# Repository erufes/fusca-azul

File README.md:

# Fusca Azul

Nova versão do robô Fusca Azul, da ERUS/UFES. O software e o hardware estão
em atualização. O reconhecimento de gestos agora usa um aplicativo desktop
em Qt, com servidor local de comandos e configuração do Wi-Fi do robô pelo navegador.

## Executar

Requer Python 3.14 ou superior, [uv](https://docs.astral.sh/uv/) e uma webcam.
Na raiz do projeto:

```bash
uv run gestos
```

No Ubuntu, Debian ou Linux Mint, instale também a biblioteca de cursor usada
pelo Qt no X11:

```bash
sudo apt-get install libxcb-cursor0
```

O uv instala as dependências e abre a janela. Na primeira execução, o aplicativo
baixa o modelo do MediaPipe, caso ele ainda não esteja disponível. As próximas
execuções podem funcionar sem internet, com as dependências e o modelo instalados.
Permita o acesso à câmera nas configurações de privacidade do sistema, se necessário.

A interface mostra a câmera espelhada, os pontos da mão, o gesto reconhecido e o
modo selecionado. Para usar outra webcam, abra a engrenagem no canto superior direito,
selecione a câmera pelo nome e clique em **Aplicar**. Se a captura estiver ativa,
o aplicativo troca a câmera automaticamente. Use **Atualizar lista** depois
de conectar ou desconectar uma webcam.

Python, Qt e MediaPipe têm versões para Linux, Windows e macOS, mas a combinação
de versões e arquitetura precisa ser compatível. No Linux, o Qt pode exigir
bibliotecas gráficas do sistema. Não há empacotamento nem Docker.

**Os gestos controlam o robô por Wi-Fi.** O aplicativo anuncia o servidor por
mDNS, e o robô o encontra automaticamente. A troca de modo pelo gesto de rock
está desabilitada, e o aplicativo permanece no modo Gestos. A navegação autônoma
ainda não foi implementada.

Veja [configuração de Wi-Fi e protocolo](docs/comunicacao.md) para conectar o robô.

## Firmware do robô

O NodeMCU/ESP8266 controla dois motores pela ponte H L298N.
O robô inicia parado e recebe frente, ré, esquerda, direita e parar da aplicação.
Sem comandos recentes ou conexão, volta a parar. O comando esquerda aciona apenas
o motor esquerdo para frente; direita aciona apenas o direito para frente, mantendo
o outro motor desligado. Os motores operam com PWM de até 100% nos pinos ENA/ENB; a parada desabilita
os canais e deixa os motores desacelerarem livremente.

| L298N | NodeMCU |
| --- | --- |
| ENA | D0 |
| IN1 | D2 |
| IN2 | D1 |
| IN3 | D3 |
| IN4 | D4 |
| ENB | D5 |

Remova os jumpers de ENA e ENB para conectar os sinais do NodeMCU. Ligue o
motor esquerdo em OUT1/OUT2 e o direito em OUT3/OUT4. Use alimentação adequada
para os motores na ponte e conecte o GND da ponte ao GND do NodeMCU.
Remova qualquer ligação antiga de sensor em D1 e D2: esses pinos controlam a ponte.
D3 e D4 precisam permanecer em nível alto durante o boot do ESP8266;
a ligação externa não deve forçá-los a nível baixo durante a inicialização.

Se uma roda girar no sentido contrário ao esperado, troque os dois fios desse
motor nas saídas da ponte, com a alimentação desligada.

A classe `Motor` abstrai cada canal da L298N, e a classe `Robot` coordena os dois
motores. Os pinos e a composição dos módulos ficam em `src/firmware/main.cpp`.
`WifiConnection` cuida do Wi-Fi e do portal, `WifiCredentials` da persistência
e `GestosConnection` da descoberta mDNS e do protocolo de comandos.
`Robot` registra as mudanças de movimento no monitor serial (115200 baud).

Para compilar e gravar com PlatformIO:

```bash
pio run
pio run --target upload
```

## Organização

- `src/gestos/application.py`: inicialização do aplicativo e logs.
- `src/gestos/ui/`: janela, visualização do vídeo e tema.
- `src/gestos/network.py`: servidor TCP, validade dos comandos e anúncio mDNS.
- `src/gestos/devices.py`: descoberta das câmeras pelo nome.
- `src/gestos/camera.py`: captura e processamento em uma thread separada.
- `src/gestos/detection.py`: integração com MediaPipe e sessão de reconhecimento.
- `src/gestos/recognition.py`: geometria e classificação dos gestos.
- `src/gestos/modes.py`: regras de troca de modo.
- `src/gestos/model.py`: localização e download do modelo.
- `src/firmware/`: firmware PlatformIO para NodeMCU/ESP8266 e ponte H L298N.
- [docs/gestos.md](docs/gestos.md): uso, gestos, modelo e logs.
- `tests/`: testes de reconhecimento, captura e interface.

A indentação usa tabs, conforme o `.editorconfig`.

Ao atualizar um ambiente da versão web, se o OpenCV apresentar erro ao abrir a
câmera, reinstale a única variante mantida pelo aplicativo. A versão anterior
instalava duas variantes que compartilhavam arquivos:

```bash
uv sync --reinstall-package opencv-contrib-python-headless
```

O projeto usa somente `opencv-contrib-python-headless`. A configuração do uv
exclui as variantes gráficas, inclusive a dependência transitiva do MediaPipe,
para evitar arquivos `cv2` sobrepostos e conflitos com os plugins do PySide6.

## Testes

```bash
uv run python -m unittest discover -s tests -v
```

Os testes da janela usam a plataforma Qt `offscreen` e câmeras simuladas;
não precisam de webcam nem do download do modelo. O uso real da câmera deve
ser verificado no computador que executa o aplicativo.

## Versão anterior

O código, a documentação, a placa e os modelos 3D antigos estão preservados no
histórico do Git, na tag anotada **v1.0.0**. Ela aponta para o
commit `7e1b7a9f1c05d8ae50a9d219d5c3933cf5e62812` da branch main, anterior à reescrita.
Não há uma cópia do legado na estrutura atual.

Para consultar um arquivo antigo sem alterar seu trabalho:

```bash
git show v1.0.0:README.md
```

Para abrir a versão antiga em uma pasta separada:

```bash
git worktree add --detach ../fusca-azul-legado v1.0.0
```

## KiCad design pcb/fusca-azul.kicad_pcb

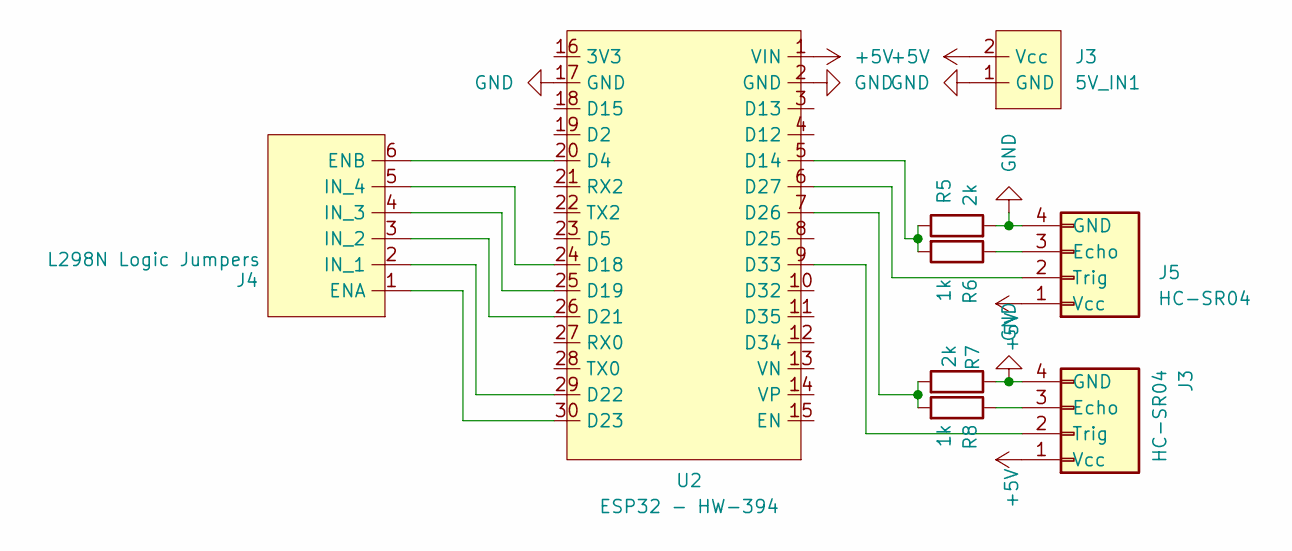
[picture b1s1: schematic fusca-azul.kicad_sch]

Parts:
5V_IN1: J3; TerminalBlock_Phoenix_MKDS-1,5-2-5.08_1x02_P5.08mm_Horizont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
J3, J5: HC-SR04; PinSocket_1x04_P2.54mm_Vertical
J4: L298N Logic Jumpers; PinSocket_1x06_P2.54mm_Vertical
R5, R7: 2k; R_Axial_DIN0207_L6.3mm_D2.5mm_P5.08mm_Vertical
R6, R8: 1k; R_Axial_DIN0207_L6.3mm_D2.5mm_P5.08mm_Vertical
U2: ESP32 - HW-394; ESP32-HW-394

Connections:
+5V: 5V_IN1.2 (Vcc), J3.1 (Vcc), J5.1 (Vcc), U2.1 (VIN)
GND: 5V_IN1.1 (GND), J3.4 (GND), J5.4 (GND), R5.2, R7.1, U2.2 (GND), U2.17 (GND)
unnamed: J3.3 (Echo), R8.1
unnamed: J3.2 (Trig), U2.9 (D33)
unnamed: J4.1 (ENA), U2.30 (D23)
unnamed: J4.6 (ENB), U2.20 (D4)
unnamed: J4.2 (IN_1), U2.29 (D22)
unnamed: J4.3 (IN_2), U2.26 (D21)
unnamed: J4.4 (IN_3), U2.25 (D19)
unnamed: J4.5 (IN_4), U2.24 (D18)
unnamed: J5.3 (Echo), R6.1
unnamed: J5.2 (Trig), U2.6 (D27)
unnamed: R5.1, R6.2, U2.5 (D14)
unnamed: R7.2, R8.2, U2.7 (D26)

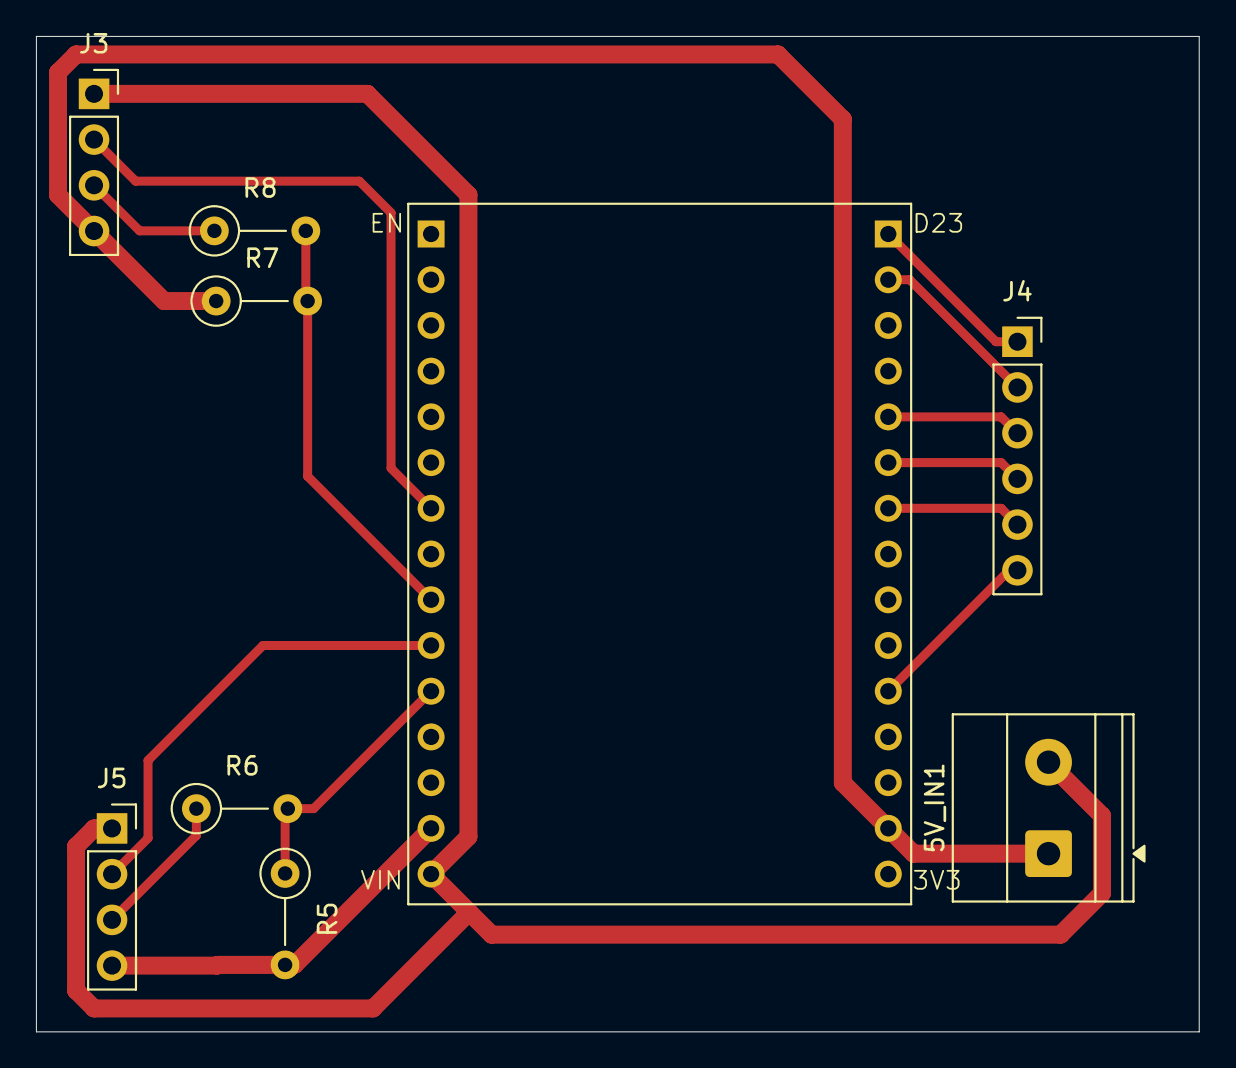
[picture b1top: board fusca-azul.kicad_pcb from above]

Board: 2 copper layers, 64.6 x 55.3 mm, 9 parts (0 on the bottom side), 14 nets.

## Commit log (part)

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2026-04-29 Add initial project structure with .gitignore, README, and mocap module
    - Created .gitignore to exclude common Python artifacts and virtual environments.
    - Added README file for project documentation.
    - Introduced mocap module with hand gesture detection functionality, including:
    - `dedos.py`: Functions to determine finger positions.
    - `gestos.py`: Class to evaluate hand gestures based on finger positions.
    - `main.py`: Main application to capture video and detect hand gestures using MediaPipe.
2026-04-29 adicionando codigo inicial do robo e gestos
2026-04-29 enviando o codigo finalizado, necessário testar
2026-04-29 correção de possiveis erros e adicao de comentario
2026-04-29 cometarios finalizados, versao "final"
2026-04-29 correcao
2026-04-30 correcao de comentarios
2026-04-30 Update de comentários
2026-04-30 adicionado codigo de teste do sensor ultrassonico
2026-04-30 correcao de nomes
2026-04-30 adicionado codigo para verificar as variaveis
2026-04-30 ADD CODIGO DO MODO 2, TESTADO E FUNCIONANDO!!
2026-05-01 adiciona simbolos e schematic do projeto feito no kicad
2026-05-01 fix: corrige posicionamento errado dos resistores
2026-05-03 feat: adiciona schematic para 3 sensores + separa schematics
2026-05-03 feat: linka schematic a footprints
2026-05-04 feat: começa a criar a pcb
2026-05-04 feat: add teste_wifi esp32
2026-05-04 - Correção bug dedão - Todos os gestos
2026-05-04 Update robo.ino
    Atualizaçao do código do robo, adicionando alguns comentários e adição da variavel distanciaMaxima, com objetivo de deixar mais prático a mudança de tal valor
2026-05-04 Update robo.ino
    corrigido nome de algumas funções, adição das variaveis de ENA e ENB
2026-05-04 Rename robo.ino to codigoRobo.ino
2026-05-05 adicao de um codigo para implementar mais sensores
2026-05-05 name changed
2026-05-05 adicao do codigo feito pra 2 sensores (esq e frent)
2026-05-05 codigo do arduinToEsp32
2026-05-06 Rename arduinToEsp32 to arduinToEsp32.ino
2026-05-08 transformando cod arduino pra esp32
2026-05-09 feat: atualiza a pcb, mas falta corrigir tamanho e organização
2026-05-10 feat: finaliza pcb
2026-05-10 fix: corrige ligacao na placa
2026-05-11 Conexão com o C++
2026-05-11 feat: adiciona arquivo 3d do robo
2026-05-11 fix: ligacao entre andares mais forte
2026-05-11 feat: adiciona objetos pra imprimir
2026-05-11 feat: adiciona buracos na base
2026-05-11 CODIGO DESVIO DE OBSTACULOS FUNCIONANDO
2026-05-11 DESVIO DE OBSTACULOS FUNCIONANDO!!!
    alterei com intuito de corrigir a direção do robo, antes curvava levemente pra esquerda
2026-05-12 excluido codigo que foi usado apenas pra teste
2026-05-12 adicionando primeira versao da integracao
2026-05-12 correcao de alguns argumentos
2026-05-12 adicao codigo de integracao
2026-05-12 add comentarios
2026-05-12 CODIGO FUNCIONANDO, ROBO CONTROLADO POR GESTOS
2026-05-13 ip trocado (wifi erus)
2026-05-13 add gesto, add deteccao de gesto no modo auto
2026-05-13 corrigido troca de modos
2026-05-13 adicionado delay na troca de modos
2026-05-13 delay da troca de modos aumentado
2026-05-13 adicionado codigo para 2 sensores ultrassonicos
2026-05-13 iniciando adicao do modo1 ao modo2
2026-05-13 Refatoração
2026-05-13 add codigo do esp 32
2026-05-14 Descrição dos gestos e da otimizção do mocap
2026-05-14 Instruções de Execução
2026-05-14 Conserto tabela gestos
2026-05-14 Conserto tabela gestos 2
2026-05-18 docs: move docs de lugar
2026-05-18 finaliza pcb
2026-05-20 Refatoração mocap
2026-05-20 Troca de IP
2026-05-20 Create espWithMilis
2026-05-21 docs: add new images for Fusca azul view
2026-05-21 corrige pcb com espaçamento erraado
2026-05-21 docs: adiciona documentação de hardware
2026-05-21 atualiza 3Ds e adiciona modelo roda
2026-05-21 docs: adiciona documentacao de estrutura
2026-05-21 docs: atualiza docs de hardware e readme
2026-05-21 update readmme
2026-05-21 Readme
2026-05-23 Projeto Final
